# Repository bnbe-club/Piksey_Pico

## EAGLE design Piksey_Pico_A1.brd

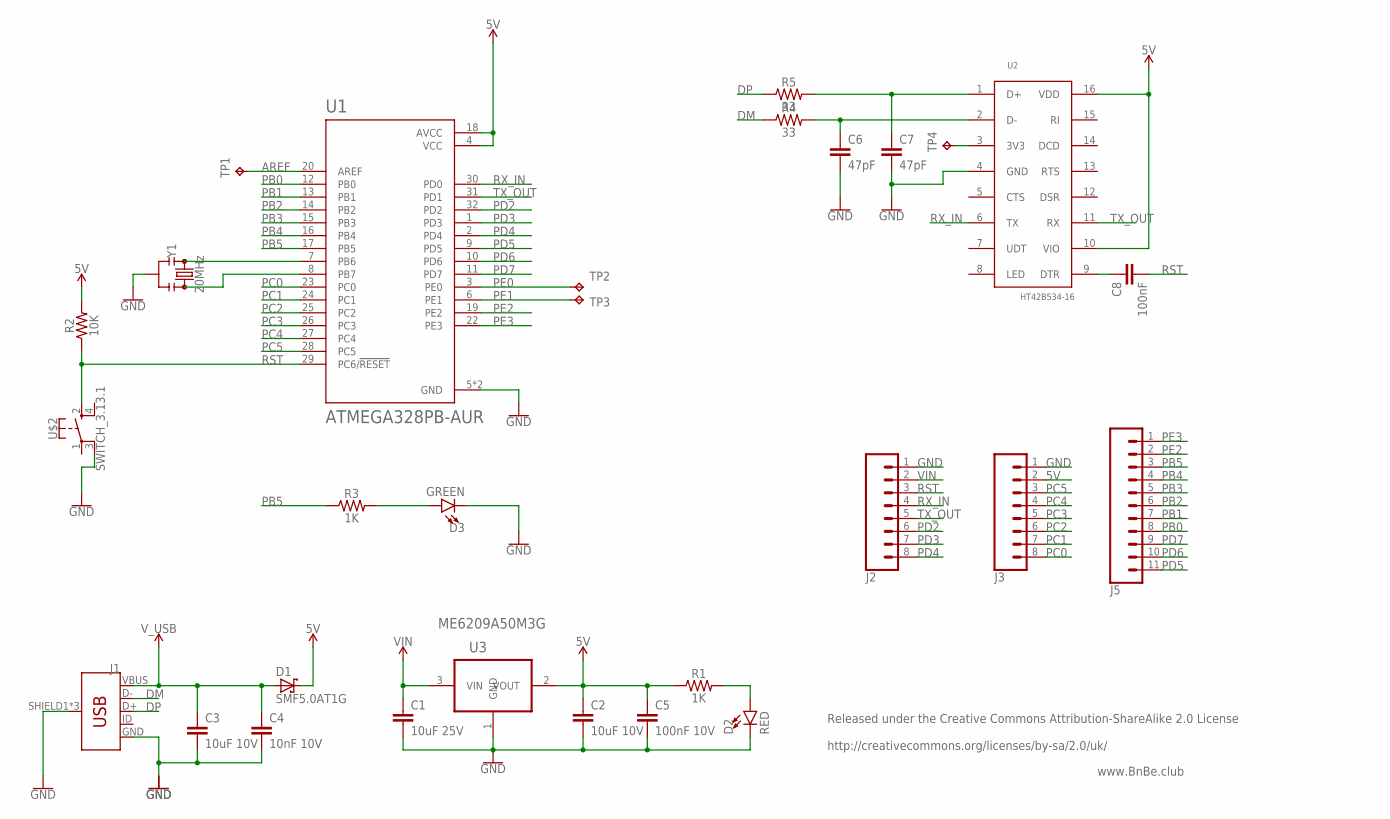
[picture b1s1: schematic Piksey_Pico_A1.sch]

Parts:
C1: 10uF 25V; 0603
C2, C3: 10uF 10V; 0402
C4: 10nF 10V; 0402
C5: 100nF 10V; 0402
C6, C7: 47pF; 0402
C8: 100nF; 0402
D1: SMF5.0AT1G; SOD123FL
D2: RED; LED-0603
D3: GREEN; LED-0603
J1: USB_MICRO-B_FEMALE-SMT; USB-B-MICRO-SMD
J2, J3: CONN_08NO_SILK_FEMALE_PTH; 1X08_NO_SILK
J5: CONN_11_1.27MM; 1X11-1.27MM
R1, R3: 1K; 0402
R2: 10K; 0402
R4, R5: 33; 0402
TP1, TP2, TP3, TP4: TPB1,27; B1,27
U1: ATMEGA328PB-AUR; QFP80P900X900X120-32N
U2: HT42B534-16; NSOP-16
U3: ME6209A50M3G; SOT95P237X112-3N
U$2: SWITCH_3.13.1; SWITCH_3.1X3.1
Y1: 20MHz; RESONATOR-SMD-3.2X1.3

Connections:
5V: C2.1, C5.1, D1.C, J3.2, R1.1, R2.2, U1.4 (VCC), U1.18 (AVCC), U2.10 (VIO), U2.16 (VDD), U3.2 (VOUT)
AREF: TP1.TP, U1.20 (AREF)
DM: J1.D-, R4.1
DP: J1.D+, R5.1
GND: C1.2, C2.2, C3.2, C4.2, C5.2, C6.2, C7.2, D2.C, D3.C, J1.GND, J1.SHIELD1 (SHIELD), J1.SHIELD2 (SHIELD), J1.SHIELD3 (SHIELD), J2.1, J3.1, U1.5 (GND), U1.21 (GND), U2.4 (GND), U3.1 (GND), U$2.3 (2), Y1.2
unnamed: TP4.TP, U2.3 (3V3)
unnamed: C7.1, R5.2, U2.1 (D+)
unnamed: U1.7 (PB6), Y1.1
unnamed: C8.1, U2.9 (DTR)
unnamed: U1.8 (PB7), Y1.3
unnamed: D2.A, R1.2
unnamed: C6.1, R4.2, U2.2 (D-)
unnamed: D3.A, R3.2
PB0: J5.8, U1.12 (PB0)
PB1: J5.7, U1.13 (PB1)
PB2: J5.6, U1.14 (PB2)
PB3: J5.5, U1.15 (PB3)
PB4: J5.4, U1.16 (PB4)
PB5: J5.3, R3.1, U1.17 (PB5)
PC0: J3.8, U1.23 (PC0)
PC1: J3.7, U1.24 (PC1)
PC2: J3.6, U1.25 (PC2)
PC3: J3.5, U1.26 (PC3)
PC4: J3.4, U1.27 (PC4)
PC5: J3.3, U1.28 (PC5)
PD2: J2.6, U1.32 (PD2)
PD3: J2.7, U1.1 (PD3)
PD4: J2.8, U1.2 (PD4)
PD5: J5.11, U1.9 (PD5)
PD6: J5.10, U1.10 (PD6)
PD7: J5.9, U1.11 (PD7)
PE0: TP2.TP, U1.3 (PE0)
PE1: TP3.TP, U1.6 (PE1)
PE2: J5.2, U1.19 (PE2)
PE3: J5.1, U1.22 (PE3)
RST: C8.2, J2.3, R2.1, U1.29 (PC6/!RESET), U$2.2 (3)
RX_IN: J2.4, U1.30 (PD0), U2.6 (TX)
TX_OUT: J2.5, U1.31 (PD1), U2.11 (RX)
VIN: C1.1, J2.2, U3.3 (VIN)
V_USB: C3.1, C4.1, D1.A, J1.VBUS

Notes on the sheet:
Released under the Creative Commons Attribution-ShareAlike 2.0 License http://creativecommons.org/licenses/by-sa/2.0/uk/
www.BnBe.club

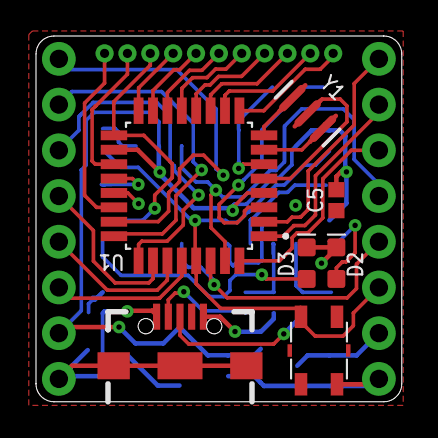
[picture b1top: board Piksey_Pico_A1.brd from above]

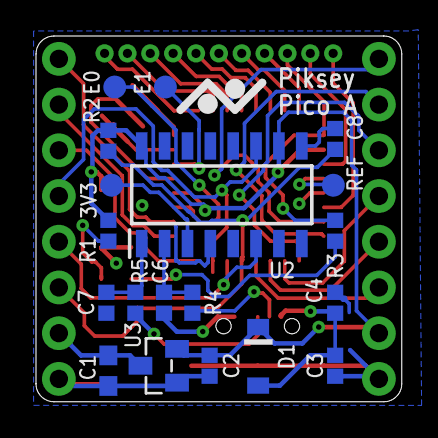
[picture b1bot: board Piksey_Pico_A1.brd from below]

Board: 2 copper layers, 20.3 x 20.3 mm, 29 parts (19 on the bottom side), 40 nets.

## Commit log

2018-12-20 Initial commit.

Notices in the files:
parts and their libraries:
SparkFun-Capacitors: Licensing: Creative Commons ShareAlike 4.0 International - https://creativecommons.org/licenses/by-sa/4.0
